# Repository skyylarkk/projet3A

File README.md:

# Robot arm project

This project is carried out by a three-students group in option Mechatronics and Complex Systems at ENSEA.

### Objectives

Our project consists in the realization of a 6-axis robot capable of catching and maintaining without damaging it a pot of yogurt. This could help people with disabilities.

### Mecanics

The mechanical part of the robot is modelled using SolidWorks software and then printed in 3D. The corresponding folder in the repository lists the various elements of the robot and their associated SolidWorks files (parts + assembly).

### Power module

In order to make the robot work, we need to build a power module to distribute the right power to every parts of the robot. The robot is powered by alternative by 230 V at 50 Hz.

### Steppers code

We chose to command the steppers with a STM32 nucleo-G431RB card. We use the STM32CubeIDE software. The different code files for the command of these steppers are present in the corresponding folder in the repository.

## To start

Here are the different instructions instructions instructions to follow to make the project work :

### Requirements

In order to make the project work, you will need the following softwares :

- STM32CubeIDE
- SolidWorks
- a software to print in 3D
- a software for PCB modeling

You also need this equipement to build your robot :

- a 3D-printer
- a STM32 Nucleo-G431RB
- 3x stepper motors with at least a 4N tork 
- 2x AX-12
- 2x XL-320
- a power conversion module from 230 V to 24 V
- all the componants to make the PCB (you can see them in the PCB files)

## Starting

In the different folders of the repository you have access to the code for the steppers, the mecanical parts and the PCB scheme for the power module of the robot.

- for the steppers code, you need to use STM32CubeIDE to upload the code on your Nucleo. Be careful to use the code from the last stable version for this project.
- for the mecanical parts, you have acces to the files you can open with SolidWorks. It is useful if you want to modify the different part ase you want, but it can possibly impact the proper functioning of the robot. You also have access to STL files of every mecanical parts in order to print it in 3D.
- for the PCB, you have all the files needed to build it in order to make the robot work.

## Built/developped with

* [STM32CubeIDE](https://www.st.com/en/development-tools/stm32cubeide.html) - for the steppers code
* [SolidWorks](https://www.solidworks.com/) - for the mecanical parts

## Versions

**Last stable version :** 1.0
**Last version :** 1.0

## Autors

* **CHAPUIS Clément** _alias_ [@ClementChapuis](https://github.com/ClementChapuis)
* **HERAULT Félix** _alias_ [@FelixHerault](https://github.com/FelixHerault)
* **SUTRA Aurélien** _alias_ [@skyylarkk](https://github.com/skyylarkk)

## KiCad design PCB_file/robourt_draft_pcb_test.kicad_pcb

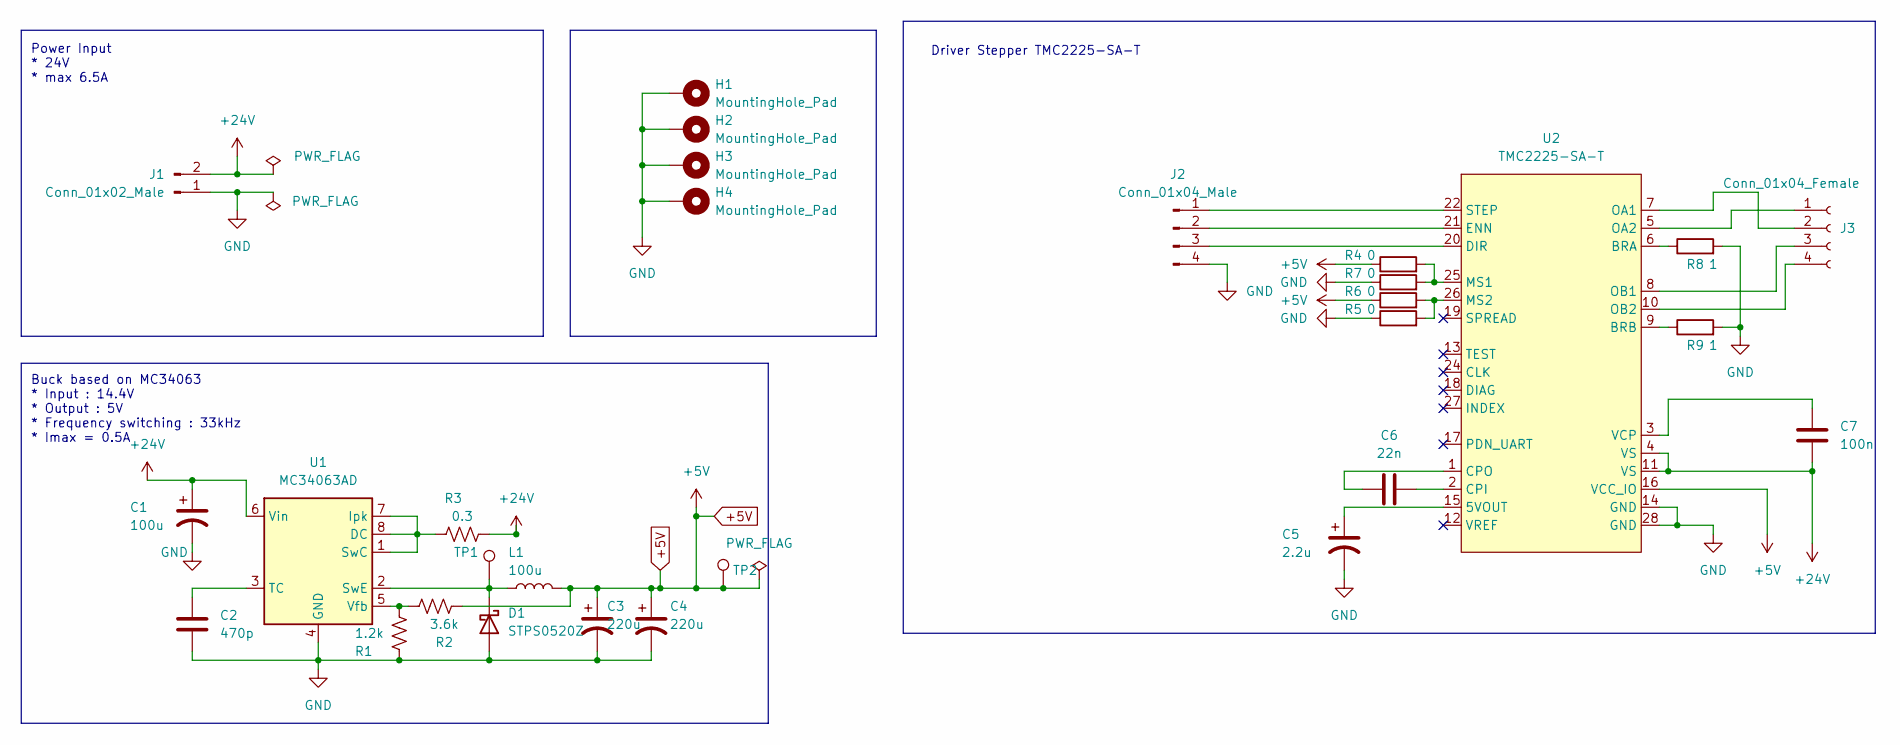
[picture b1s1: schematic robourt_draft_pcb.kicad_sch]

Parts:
C1: 100u; CP_Elec_6.3x7.7
C2: 470p; C_0603_1608Metric_Pad1.08x0.95mm_HandSolder
C3, C4: 220u; CP_Elec_8x10.5
C5: 2.2u; CP_Elec_4x5.7
C6: 22n; C_0603_1608Metric_Pad1.08x0.95mm_HandSolder
C7: 100n; C_0603_1608Metric_Pad1.08x0.95mm_HandSolder
D1: STPS0520Z; D_SOD-123
H1, H2, H3, H4: MountingHole_Pad; MountingHole_3.2mm_M3_DIN965_Pad
J1: Conn_01x02_Male; AMASS_XT60-M_1x02_P7.20mm_Vertical
J2: Conn_01x04_Male; PinHeader_1x04_P2.54mm_Vertical
J3: Conn_01x04_Female; PinSocket_1x04_P2.54mm_Vertical
L1: 100u; L_12x12mm_H6mm
R1: 1.2k; R_0603_1608Metric_Pad0.98x0.95mm_HandSolder
R2: 3.6k; R_0603_1608Metric_Pad0.98x0.95mm_HandSolder
R3: 0.3; R_0603_1608Metric_Pad0.98x0.95mm_HandSolder
R4, R5, R6, R7: 0; R_0603_1608Metric_Pad0.98x0.95mm_HandSolder
R8, R9: 1; R_0603_1608Metric_Pad0.98x0.95mm_HandSolder
TP1: BUCK_OUT; TestPoint_Pad_D1.0mm
TP2: +5V; TestPoint_Pad_D1.0mm
U1: MC34063AD; SOIC-8_3.9x4.9mm_P1.27mm
U2: TMC2225-SA-T; HTSSOP-28-1EP_4.4x9.7mm_P0.65mm_EP2.85x5.4mm_ThermalVias

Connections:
+5V: C3.1, C4.1, L1.2, R2.2, R4.1, R6.1, TP2.1, U2.16 (VCC_IO)
+24V: C1.1, C7.2, J1.2, R3.2, U1.6 (Vin), U2.4 (VS), U2.11 (VS)
GND: C1.2, C2.2, C3.2, C4.2, C5.2, D1.2 (A), H1.1, H2.1, H3.1, H4.1, J1.1, J2.4, R1.2, R5.1, R7.1, R8.2, R9.2, U1.4 (GND), U2.14 (GND), U2.28 (GND)
unnamed: C2.1, U1.3 (TC)
unnamed: C6.1, U2.1 (CPO)
unnamed: C6.2, U2.2 (CPI)
unnamed: C7.1, U2.3 (VCP)
unnamed: D1.1 (K), L1.1, TP1.1, U1.2 (SwE)
unnamed: J2.1, U2.22 (STEP)
unnamed: J2.2, U2.21 (ENN)
unnamed: J2.3, U2.20 (DIR)
unnamed: J3.3, U2.8 (OB1)
unnamed: J3.4, U2.10 (OB2)
unnamed: R1.1, R2.1, U1.5 (Vfb)
unnamed: R3.1, U1.1 (SwC), U1.7 (Ipk), U1.8 (DC)
unnamed: R4.2, R5.2, U2.25 (MS1)
unnamed: R6.2, R7.2, U2.26 (MS2)
unnamed: R8.1, U2.6 (BRA)
unnamed: R9.1, U2.9 (BRB)
unnamed: J3.1, U2.5 (OA2)
unnamed: J3.2, U2.7 (OA1)
unnamed: C5.1, U2.15 (5VOUT)

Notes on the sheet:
Driver Stepper TMC2225-SA-T
Buck based on MC34063 * Input : 14.4V * Output : 5V * Frequency switching : 33kHz * Imax = 0.5A
Power Input * 24V * max 6.5A

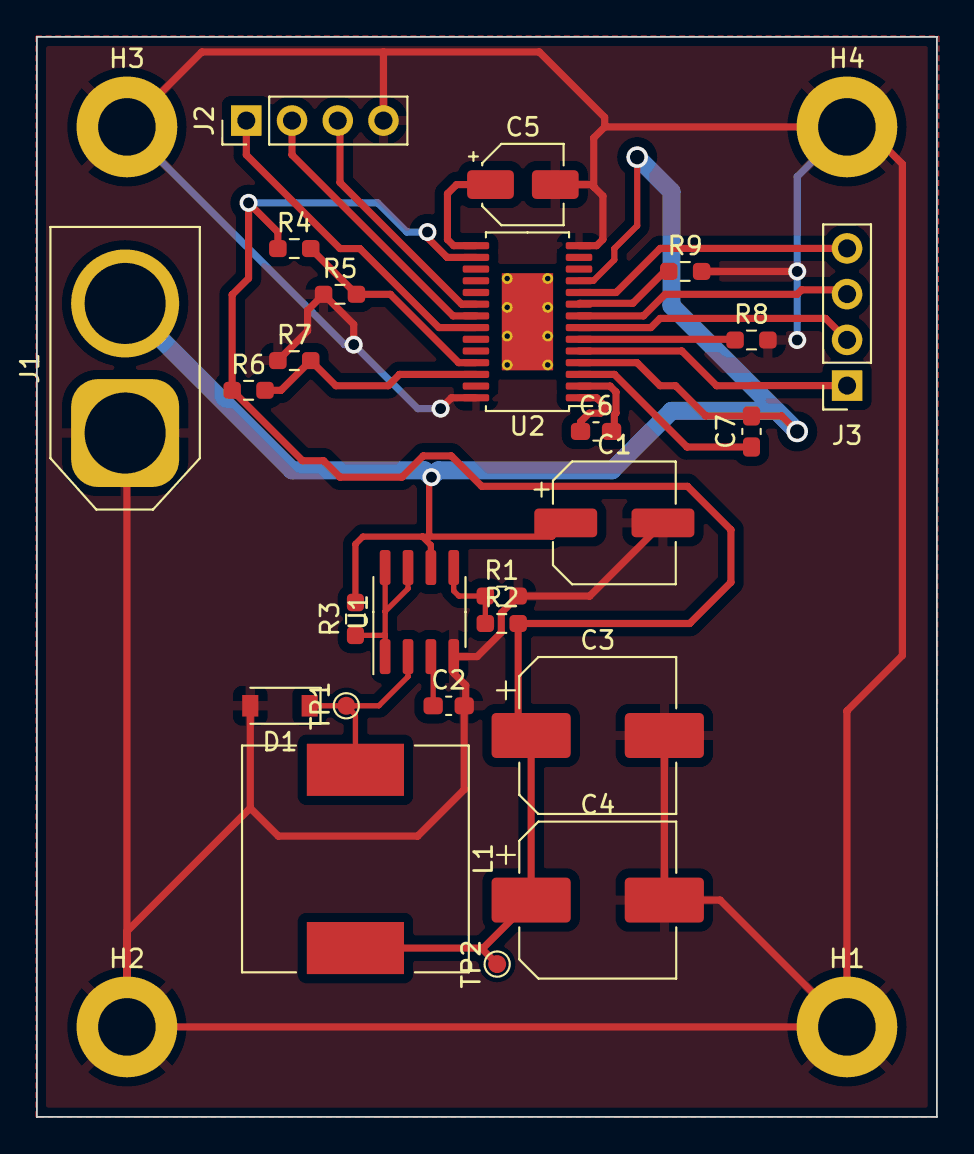
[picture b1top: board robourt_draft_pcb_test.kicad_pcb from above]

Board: 2 copper layers, 50.0 x 60.0 mm, 29 parts (0 on the bottom side), 22 nets.
